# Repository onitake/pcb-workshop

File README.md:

PCB layouting workshop
======================

These are the example files and a short presentation for an
introduction to printed circuit board layouting with KiCad.

The design is loosely based on [Larry Ogrodnek's nametag](http://analogmachines.com/p/nametag/build/),
with some modifications and enhancements.
There's both through-hole and SMD versions.
The THT version is designed for 5mm LEDs, thus making it very
large. A new 3mm version is being worked on.

The software for the microcontroller is in [a separate project](https://github.com/nuess0r/am-nametag).

You can also find an example for a LED dot matrix display tag.
(currently broken, the pinout is wrong)

Description
-----------

The circuit is grouped in 4 parts:
- 5 LED blocks
- Transistor drivers for each block (based on 2N7002 N-FETs)
- ATtiny13 microcontoller
- CR2032 battery

Each block consists of a total of 20 LEDs in parallel, which can be
soldered on as desired.

It should be noted that the CR2032 has a high internal resistance
and can only deliver small currents, up to about 40mA.

The current-limiting resistors for each block should thus be
adjusted accordingly, to prevent brown-out of the MCU.
Note that the transistors also have a relatively high
on resistance.

If a Li-Ion or LiPo battery is used instead of the button
cell, much higher currents are possible.

The parts are fairly standard and can be ordered from any
supplier, such as Farnell, DigiKey, Reichelt, ...

License
-------

This documentation is copyright © 2016 by Chaostreff Basel and
describes Open Hardware and is licensed under the CERN OHL v. 1.2.
Please see the the [LICENSE](LICENSE) file for applicable conditions.

The author's contact information can be found in [AUTHORS](AUTHORS).

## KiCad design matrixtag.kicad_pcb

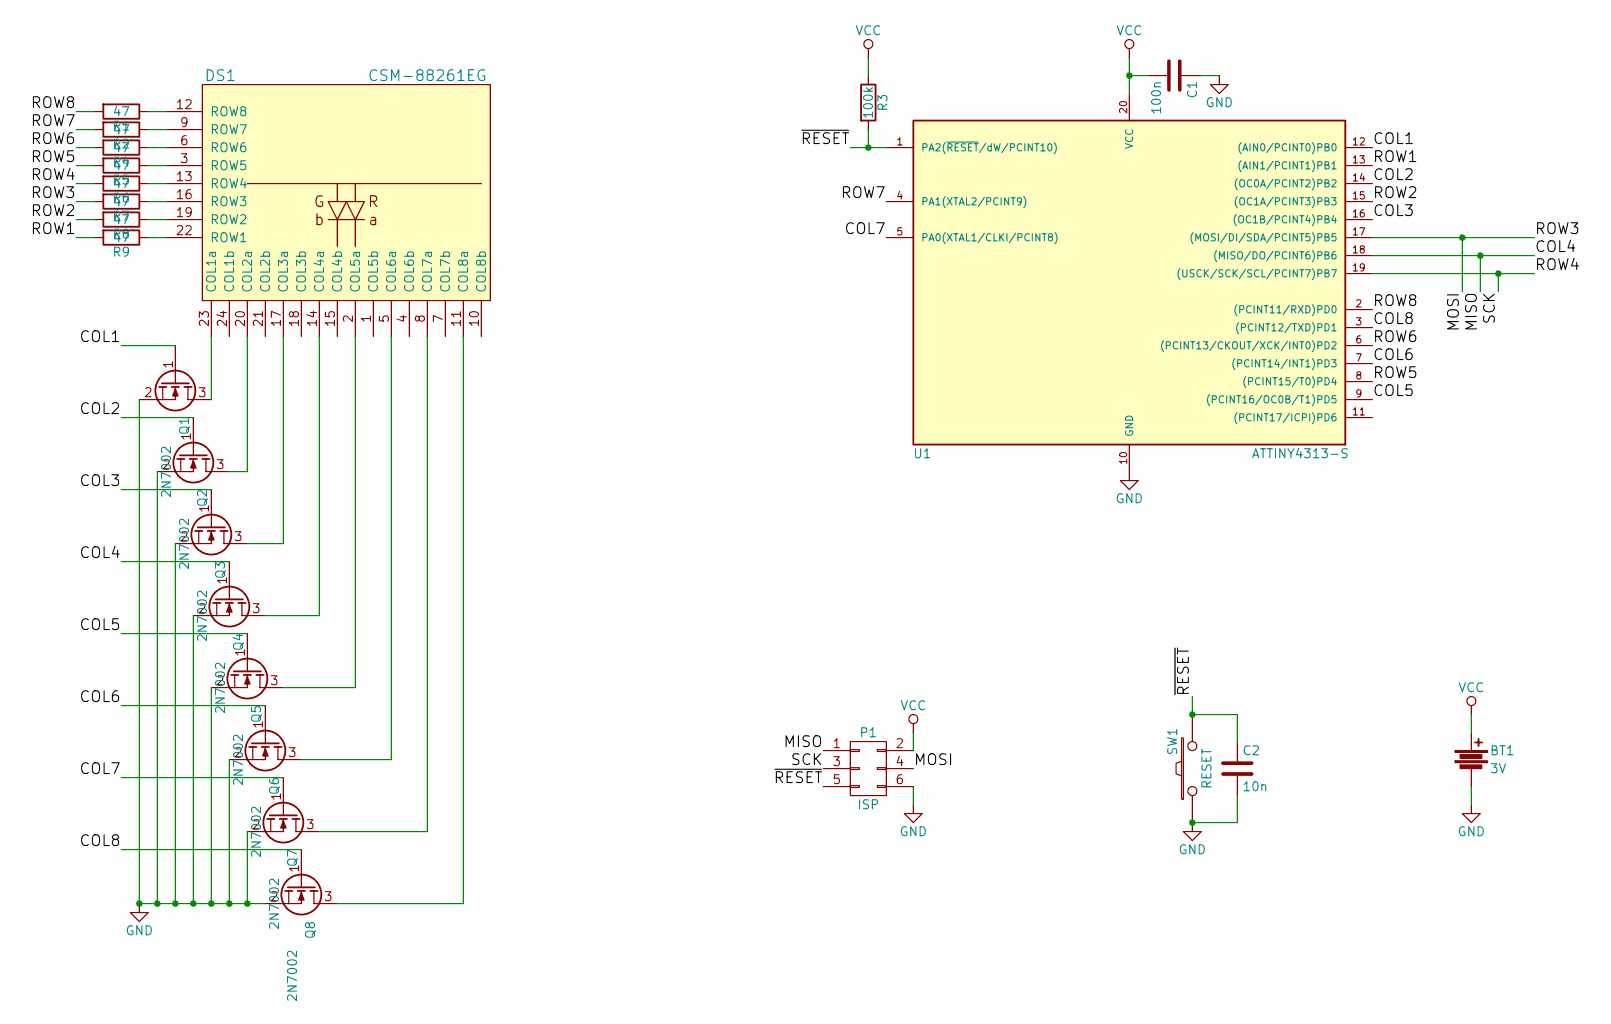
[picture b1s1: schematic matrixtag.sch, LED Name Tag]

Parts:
BT1: 3V; CR2032
C1: 100n; C_0805_HandSoldering
C2: 10n; C_0805_HandSoldering
DS1: CSM-88261EG; CSM-88261
P1: ISP; Pin_Header_Straight_2x03
Q1, Q2, Q3, Q4, Q5, Q6, Q7, Q8: 2N7002; SOT-23_Handsoldering
R1, R2, R4, R5, R6, R7, R8, R9: 47; R_0805_HandSoldering
R3: 100k; R_0805_HandSoldering
SW1: RESET; SW_PUSH_SMALL
U1: ATTINY4313-S; SOIC-20_7.5x12.8mm_Pitch1.27mm

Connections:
/COL1: Q1.1 (G), U1.12 ((AIN0/PCINT0)PB0)
/COL2: Q2.1 (G), U1.14 ((OC0A/PCINT2)PB2)
/COL3: Q3.1 (G), U1.16 ((OC1B/PCINT4)PB4)
/COL4: P1.1, Q4.1 (G), U1.18 ((MISO/DO/PCINT6)PB6)
/COL5: Q5.1 (G), U1.9 ((PCINT16/OC0B/T1)PD5)
/COL6: Q6.1 (G), U1.7 ((PCINT14/INT1)PD3)
/COL7: Q7.1 (G), U1.5 (PA0(XTAL1/CLKI/PCINT8))
/COL8: Q8.1 (G), U1.3 ((PCINT12/TXD)PD1)
/MOSI: P1.4, R7.2, U1.17 ((MOSI/DI/SDA/PCINT5)PB5)
/ROW1: R9.2, U1.13 ((AIN1/PCINT1)PB1)
/ROW2: R8.2, U1.15 ((OC1A/PCINT3)PB3)
/ROW4: P1.3, R6.2, U1.19 ((USCK/SCK/SCL/PCINT7)PB7)
/ROW5: R5.2, U1.8 ((PCINT15/T0)PD4)
/ROW6: R4.2, U1.6 ((PCINT13/CKOUT/XCK/INT0)PD2)
/ROW7: R2.2, U1.4 (PA1(XTAL2/PCINT9))
/ROW8: R1.2, U1.2 ((PCINT11/RXD)PD0)
/~RESET: C2.1, P1.5, R3.2, SW1.2, U1.1 (PA2(~RESET~/dW/PCINT10))
GND: BT1.2, C1.1, C2.2, P1.6, Q1.2 (S), Q2.2 (S), Q3.2 (S), Q4.2 (S), Q5.2 (S), Q6.2 (S), Q7.2 (S), Q8.2 (S), SW1.1, U1.10 (GND)
unnamed: DS1.2 (COL5a), Q5.3 (D)
unnamed: DS1.3 (ROW5), R5.1
unnamed: DS1.5 (COL6a), Q6.3 (D)
unnamed: DS1.6 (ROW6), R4.1
unnamed: DS1.8 (COL7a), Q7.3 (D)
unnamed: DS1.9 (ROW7), R2.1
unnamed: DS1.11 (COL8a), Q8.3 (D)
unnamed: DS1.12 (ROW8), R1.1
unnamed: DS1.13 (ROW4), R6.1
unnamed: DS1.14 (COL4a), Q4.3 (D)
unnamed: DS1.16 (ROW3), R7.1
unnamed: DS1.17 (COL3a), Q3.3 (D)
unnamed: DS1.19 (ROW2), R8.1
unnamed: DS1.20 (COL2a), Q2.3 (D)
unnamed: DS1.22 (ROW1), R9.1
unnamed: DS1.23 (COL1a), Q1.3 (D)
VCC: BT1.1, C1.2, P1.2, R3.1, U1.20 (VCC)

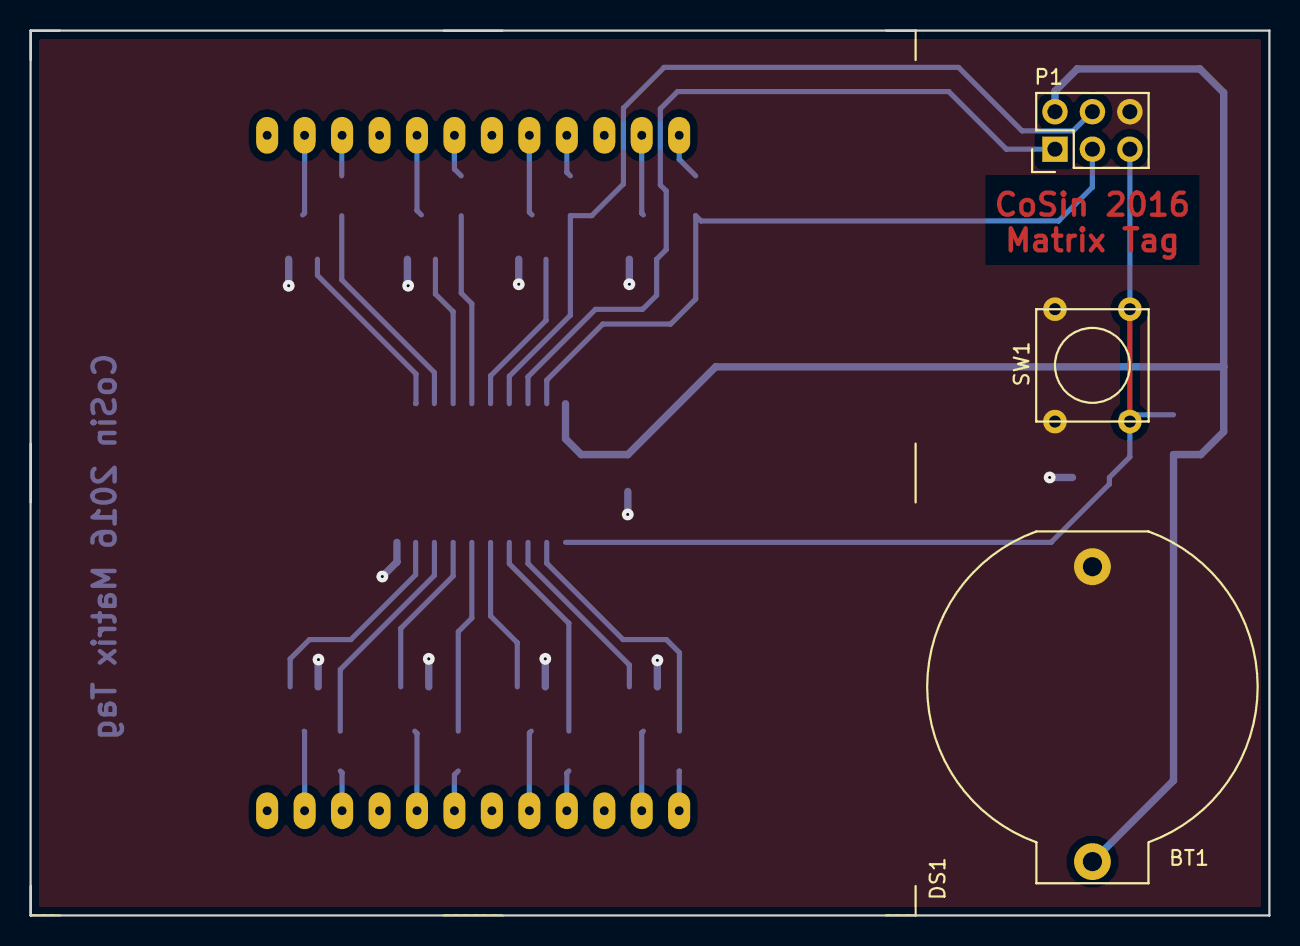
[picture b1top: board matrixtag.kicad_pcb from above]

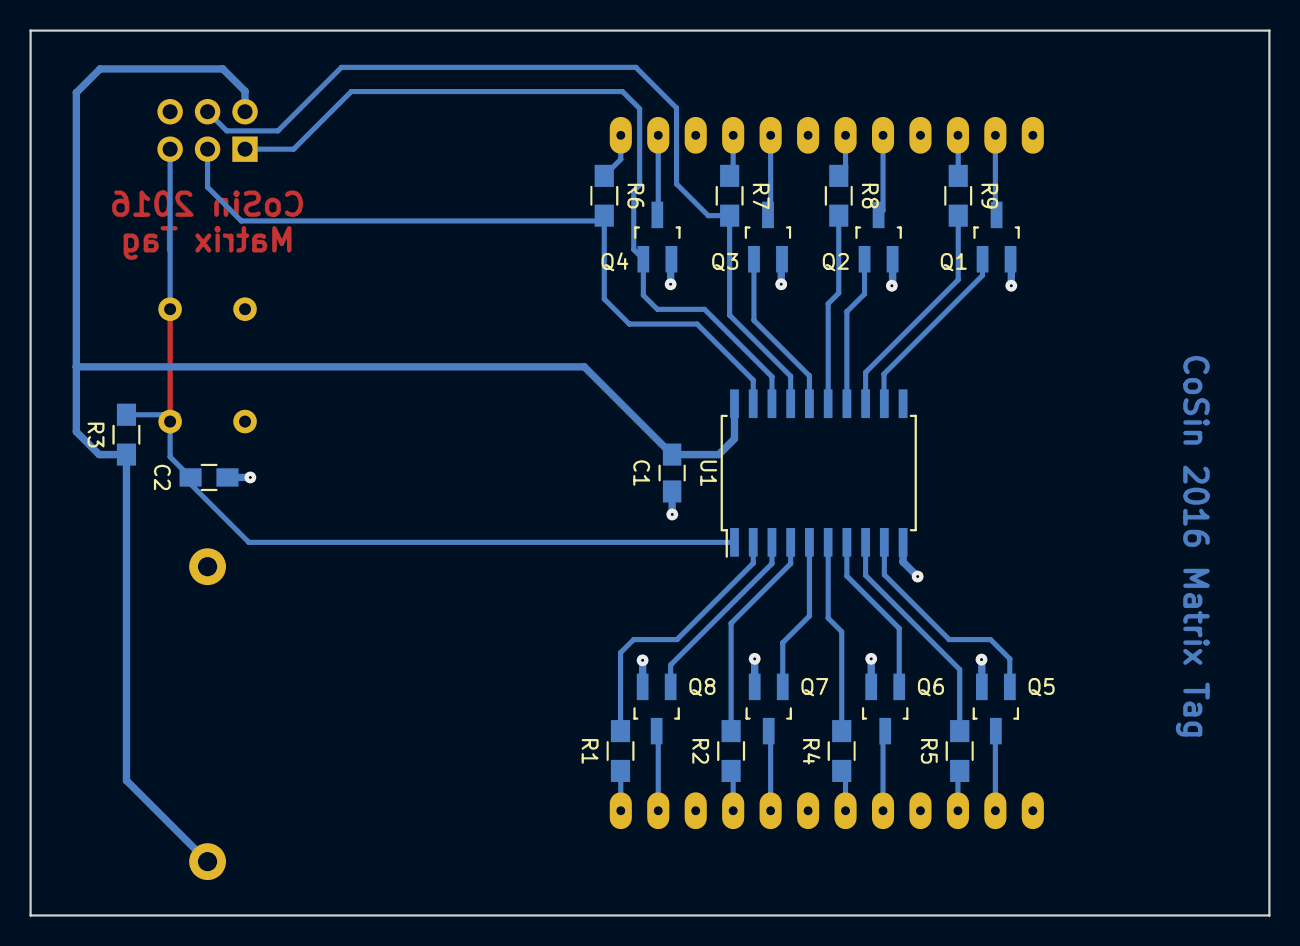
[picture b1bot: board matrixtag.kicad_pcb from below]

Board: 2 copper layers, 84.0 x 60.0 mm, 24 parts (20 on the bottom side), 35 nets.

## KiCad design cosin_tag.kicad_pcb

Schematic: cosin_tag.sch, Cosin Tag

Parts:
BT1: 3V; CR2032
C2: 100n; R_1206_HandSoldering
D1, D2, D3, D4, D5, D6, D7, D8, D9, D10, D21, D22, D23, D24, D25, D26, D27, D28, D29, D30, D31, D32, D41, D42, D43, D44, D45, D46, D47, D48, D49, D50, D51, D61, D62, D63, D64, D65, D81, D82, D83, D84, D85, D86, D87, D88, D89, D90, D91: LED; LED_0805
IC1: ATTINY13-SS; SOIC-8-N
JP1: RESET; SW_SPST_EVQP0
P1: ISP; Pin_Header_Straight_2x03
Q1, Q2, Q3, Q4, Q5: 2N7002; SOT-23_Handsoldering
R1, R2, R3, R4, R5: 0; R_0603_HandSoldering
R6: 100k; R_0603_HandSoldering

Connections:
/DIGIT0: IC1.2, Q1.1 (G)
/DIGIT1: IC1.3, Q2.1 (G)
/DIGIT2: IC1.7, P1.3, Q3.1 (G)
/DIGIT3: IC1.5, P1.4, Q4.1 (G)
/DIGIT4: IC1.6, P1.1, Q5.1 (G)
/~RESET: IC1.1, JP1.2, P1.5, R6.2
GND: BT1.2, C2.2, IC1.4, JP1.1, P1.6, Q1.2 (S), Q2.2 (S), Q3.2 (S), Q4.2 (S), Q5.2 (S)
unnamed: D1.1 (K), D2.1 (K), D3.1 (K), D4.1 (K), D5.1 (K), D6.1 (K), D7.1 (K), D8.1 (K), D9.1 (K), D10.1 (K), Q1.3 (D)
unnamed: D1.2 (A), D2.2 (A), D3.2 (A), D4.2 (A), D5.2 (A), D6.2 (A), D7.2 (A), D8.2 (A), D9.2 (A), D10.2 (A), R1.2
unnamed: D21.1 (K), D22.1 (K), D23.1 (K), D24.1 (K), D25.1 (K), D26.1 (K), D27.1 (K), D28.1 (K), D29.1 (K), D30.1 (K), D31.1 (K), D32.1 (K), Q2.3 (D)
unnamed: D21.2 (A), D22.2 (A), D23.2 (A), D24.2 (A), D25.2 (A), D26.2 (A), D27.2 (A), D28.2 (A), D29.2 (A), D30.2 (A), D31.2 (A), D32.2 (A), R2.2
unnamed: D41.1 (K), D42.1 (K), D43.1 (K), D44.1 (K), D45.1 (K), D46.1 (K), D47.1 (K), D48.1 (K), D49.1 (K), D50.1 (K), D51.1 (K), Q3.3 (D)
unnamed: D41.2 (A), D42.2 (A), D43.2 (A), D44.2 (A), D45.2 (A), D46.2 (A), D47.2 (A), D48.2 (A), D49.2 (A), D50.2 (A), D51.2 (A), R3.2
unnamed: D61.1 (K), D62.1 (K), D63.1 (K), D64.1 (K), D65.1 (K), Q4.3 (D)
unnamed: D61.2 (A), D62.2 (A), D63.2 (A), D64.2 (A), D65.2 (A), R4.2
unnamed: D81.1 (K), D82.1 (K), D83.1 (K), D84.1 (K), D85.1 (K), D86.1 (K), D87.1 (K), D88.1 (K), D89.1 (K), D90.1 (K), D91.1 (K), Q5.3 (D)
unnamed: D81.2 (A), D82.2 (A), D83.2 (A), D84.2 (A), D85.2 (A), D86.2 (A), D87.2 (A), D88.2 (A), D89.2 (A), D90.2 (A), D91.2 (A), R5.2
VCC: BT1.1, C2.1, IC1.8, P1.2, R1.1, R2.1, R3.1, R4.1, R5.1, R6.1

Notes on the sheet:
Coincell battery holder CR2032

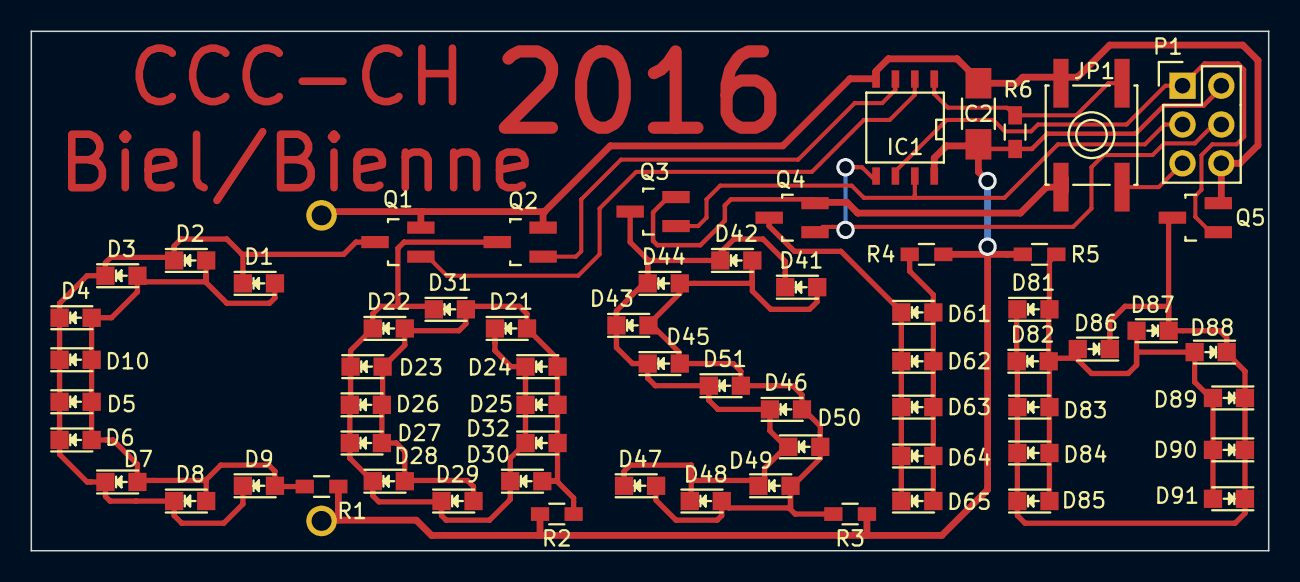
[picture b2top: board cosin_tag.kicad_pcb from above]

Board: 2 copper layers, 81.0 x 34.0 mm, 65 parts (1 on the bottom side), 18 nets.

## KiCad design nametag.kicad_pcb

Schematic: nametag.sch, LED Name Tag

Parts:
BT1: 3V; CR2032
C2: 100n; C_Disc_D3_P2.5
D1, D2, D3, D4, D5, D6, D7, D8, D9, D10, D11, D12, D13, D14, D15, D16, D17, D18, D19, D20, D21, D22, D23, D24, D25, D26, D27, D28, D29, D30, D31, D32, D33, D34, D35, D36, D37, D38, D39, D40, D41, D42, D43, D44, D45, D46, D47, D48, D49, D50, D51, D52, D53, D54, D55, D56, D57, D58, D59, D60, D61, D62, D63, D64, D65, D66, D67, D68, D69, D70, D71, D72, D73, D74, D75, D76, D77, D78, D79, D80, D81, D82, D83, D84, D85, D86, D87, D88, D89, D90, D91, D92, D93, D94, D95, D96, D97, D98, D99, D100: LED; LED-5MM
JP1: RESET; SW_PUSH_SMALL
P1: ISP; Pin_Header_Straight_2x03
Q1, Q2, Q3, Q4, Q5: 2N7002; SOT-23_Handsoldering
R1, R2, R3, R4, R5: 0; Resistor_Horizontal_RM10mm
R6: 100k; Resistor_Horizontal_RM10mm
U1: ATTINY13-SS; DIP-8_W7.62mm

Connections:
/DIGIT0: Q1.1 (G), U1.2
/DIGIT1: Q2.1 (G), U1.3
/DIGIT2: P1.3, Q3.1 (G), U1.7
/DIGIT3: P1.4, Q4.1 (G), U1.5
/DIGIT4: P1.1, Q5.1 (G), U1.6
/~RESET: JP1.1, P1.5, R6.2, U1.1
GND: BT1.2, C2.2, JP1.2, P1.6, Q1.2 (S), Q2.2 (S), Q3.2 (S), Q4.2 (S), Q5.2 (S), U1.4
unnamed: D1.1 (K), D2.1 (K), D3.1 (K), D4.1 (K), D5.1 (K), D6.1 (K), D7.1 (K), D8.1 (K), D9.1 (K), D10.1 (K), D11.1 (K), D12.1 (K), D13.1 (K), D14.1 (K), D15.1 (K), D16.1 (K), D17.1 (K), D18.1 (K), D19.1 (K), D20.1 (K), Q1.3 (D)
unnamed: D1.2 (A), D2.2 (A), D3.2 (A), D4.2 (A), D5.2 (A), D6.2 (A), D7.2 (A), D8.2 (A), D9.2 (A), D10.2 (A), D11.2 (A), D12.2 (A), D13.2 (A), D14.2 (A), D15.2 (A), D16.2 (A), D17.2 (A), D18.2 (A), D19.2 (A), D20.2 (A), R1.2
unnamed: D21.1 (K), D22.1 (K), D23.1 (K), D24.1 (K), D25.1 (K), D26.1 (K), D27.1 (K), D28.1 (K), D29.1 (K), D30.1 (K), D31.1 (K), D32.1 (K), D33.1 (K), D34.1 (K), D35.1 (K), D36.1 (K), D37.1 (K), D38.1 (K), D39.1 (K), D40.1 (K), Q2.3 (D)
unnamed: D21.2 (A), D22.2 (A), D23.2 (A), D24.2 (A), D25.2 (A), D26.2 (A), D27.2 (A), D28.2 (A), D29.2 (A), D30.2 (A), D31.2 (A), D32.2 (A), D33.2 (A), D34.2 (A), D35.2 (A), D36.2 (A), D37.2 (A), D38.2 (A), D39.2 (A), D40.2 (A), R2.2
unnamed: D41.1 (K), D42.1 (K), D43.1 (K), D44.1 (K), D45.1 (K), D46.1 (K), D47.1 (K), D48.1 (K), D49.1 (K), D50.1 (K), D51.1 (K), D52.1 (K), D53.1 (K), D54.1 (K), D55.1 (K), D56.1 (K), D57.1 (K), D58.1 (K), D59.1 (K), D60.1 (K), Q3.3 (D)
unnamed: D41.2 (A), D42.2 (A), D43.2 (A), D44.2 (A), D45.2 (A), D46.2 (A), D47.2 (A), D48.2 (A), D49.2 (A), D50.2 (A), D51.2 (A), D52.2 (A), D53.2 (A), D54.2 (A), D55.2 (A), D56.2 (A), D57.2 (A), D58.2 (A), D59.2 (A), D60.2 (A), R3.2
unnamed: D61.1 (K), D62.1 (K), D63.1 (K), D64.1 (K), D65.1 (K), D66.1 (K), D67.1 (K), D68.1 (K), D69.1 (K), D70.1 (K), D71.1 (K), D72.1 (K), D73.1 (K), D74.1 (K), D75.1 (K), D76.1 (K), D77.1 (K), D78.1 (K), D79.1 (K), D80.1 (K), Q4.3 (D)
unnamed: D61.2 (A), D62.2 (A), D63.2 (A), D64.2 (A), D65.2 (A), D66.2 (A), D67.2 (A), D68.2 (A), D69.2 (A), D70.2 (A), D71.2 (A), D72.2 (A), D73.2 (A), D74.2 (A), D75.2 (A), D76.2 (A), D77.2 (A), D78.2 (A), D79.2 (A), D80.2 (A), R4.2
unnamed: D81.1 (K), D82.1 (K), D83.1 (K), D84.1 (K), D85.1 (K), D86.1 (K), D87.1 (K), D88.1 (K), D89.1 (K), D90.1 (K), D91.1 (K), D92.1 (K), D93.1 (K), D94.1 (K), D95.1 (K), D96.1 (K), D97.1 (K), D98.1 (K), D99.1 (K), D100.1 (K), Q5.3 (D)
unnamed: D81.2 (A), D82.2 (A), D83.2 (A), D84.2 (A), D85.2 (A), D86.2 (A), D87.2 (A), D88.2 (A), D89.2 (A), D90.2 (A), D91.2 (A), D92.2 (A), D93.2 (A), D94.2 (A), D95.2 (A), D96.2 (A), D97.2 (A), D98.2 (A), D99.2 (A), D100.2 (A), R5.2
VCC: BT1.1, C2.1, P1.2, R1.1, R2.1, R3.1, R4.1, R5.1, R6.1, U1.8

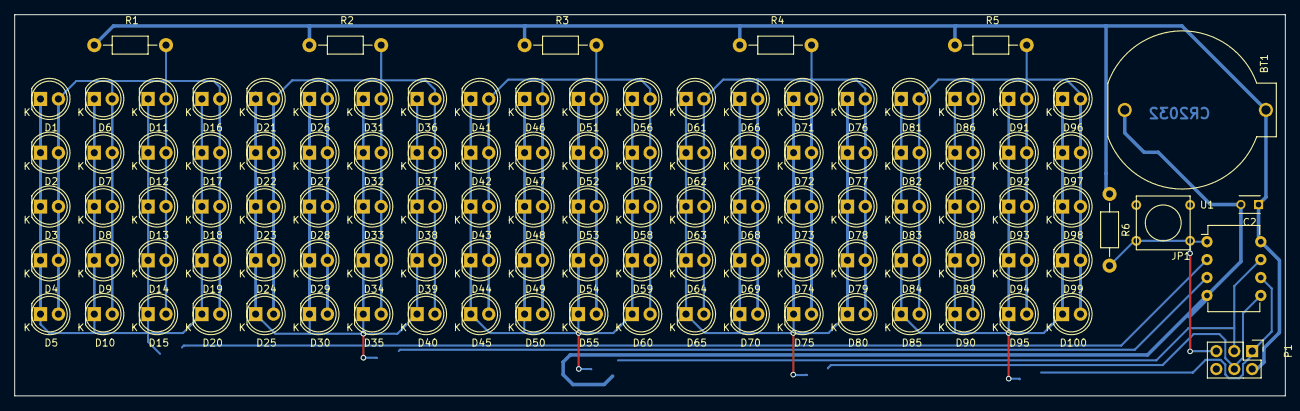
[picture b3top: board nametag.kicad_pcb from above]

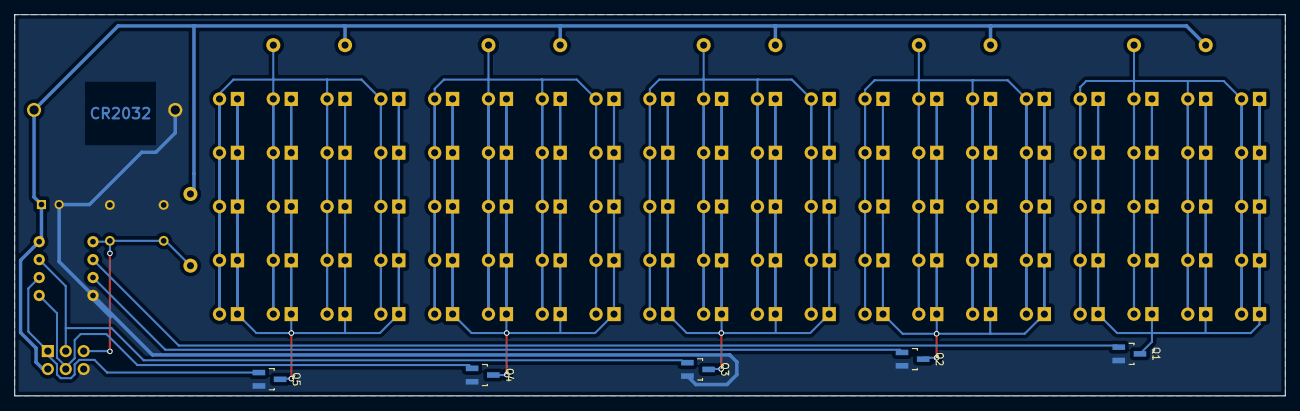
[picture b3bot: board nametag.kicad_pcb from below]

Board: 2 copper layers, 180.0 x 54.0 mm, 116 parts (5 on the bottom side), 18 nets.

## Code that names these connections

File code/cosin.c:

/* 
 * cosin.c
 * 
 * CoSin 2016 LED Matrix Tag
 * Controller firmware
 * 
 * Copyright (c) 2016 Gregor Riepl <onitake@gmail.com>
 * 
 * This documentation describes Open Hardware and is licensed under the
 * CERN OHL v. 1.1.
 * You may redistribute and modify this documentation under the terms of the
 * CERN OHL v.1.1. (http://ohwr.org/cernohl). This documentation is distributed
 * WITHOUT ANY EXPRESS OR IMPLIED WARRANTY, INCLUDING OF
 * MERCHANTABILITY, SATISFACTORY QUALITY AND FITNESS FOR A
 * PARTICULAR PURPOSE. Please see the CERN OHL v.1.1 for applicable
 * conditions
*/

#include <avr/io.h>
#include <avr/interrupt.h>
#include <avr/pgmspace.h>
#include <util/delay.h>
#include <stdint.h>
#include <stdbool.h>
#include <string.h>
#include "map.h"

// Global state
struct {
	// The framebuffer
	// in column-major order
	uint8_t fb[8];
	// Current column
	uint8_t col;
	// Letter index
	uint8_t scene;
	// Horizontal offset
	uint8_t offset;
} global __attribute__((section(".noinit")));

const char MESSAGE[] PROGMEM = "COSIN 2016 ";
extern const unsigned char FONT_SANS8X8[][8] PROGMEM;
extern const unsigned char FONTMAP_SANS8X8[] PROGMEM;

// Initalize ports and timers
void init() {
	global.col = 0;
	memset(global.fb, 0, 8*8);
	global.scene = 0;
	global.offset = 0;

	PORTB &= ~0xff;
	DDRB |= 0xff;
	PORTD &= ~0x3f;
	DDRD |= 0x3f;
	PORTA &= ~0x03;
	DDRA |= 0x03;
	
	OCR1A = F_CPU / 1024 / 8;
	TIMSK |= _BV(TOIE1);
	// Fast PWM, TOP in OCR1A
	TCCR1A = _BV(WGM11) | _BV(WGM10);
	// CLKio / 1024
	TCCR1B = _BV(WGM13) | _BV(WGM12) | _BV(CS12) | _BV(CS10);
}

// Write a letter to the framebuffer
void wrletter(char letter, int8_t xoffset) {
	uint8_t xstart, xlen;
	if (xoffset < 0) {
		if (xoffset >= -8) {
			xstart = -xoffset;
			xlen = 8 + xoffset;
		} else {
			xstart = 0;
			xlen = 0;
		}
		xoffset = 0;
	} else if (xoffset >= 0) {
		if (xoffset < 8) {
			xlen = 8 - xoffset;
		} else {
			xlen = 0;
		}
		xstart = 0;
	}
	if (xlen > 0) {
		uint8_t index = pgm_read_byte(&FONTMAP_SANS8X8[(uint8_t) letter]);
		memcpy_P(global.fb + xoffset, FONT_SANS8X8[index] + xstart, xlen);
	}
}

// Refresh the display (one column at a time)
void refresh() {
	// Port map
	// COL1: PB1
	// COL2: PB3
	// COL3: PB5
	// COL4: PB7
	// COL5: PD5
	// COL6: PD3
	// COL7: PA0
	// COL8: PD1
	// ROW1: PB0
	// ROW2: PB2
	// ROW3: PB4
	// ROW4: PB6
	// ROW5: PD4
	// ROW6: PD2
	// ROW7: PA1
	// ROW8: PD0
	
	// Wiring
	// COL is driven by MOSFETs, while ROW is driven directly by MCU
	// Switch COL first, then present ROW bit pattern
	
	uint8_t bitmap = global.fb[global.col];
	uint8_t pa = 0, pb = 0, pd = 0;

	// switch is no good here - it will make avr-gcc allocate and
	// initialize 18 bytes of .data space for the lookup table - WTF!
	uint8_t col = global.col;
	if (col == 0) {
		pb |= _BV(1);
	} else if (col == 1) {
		pb |= _BV(3);
	} else if (col == 2) {
		pb |= _BV(5);
	} else if (col == 3) {
		pb |= _BV(7);
	} else if (col == 4) {
		pd |= _BV(5);
	} else if (col == 5) {
		pd |= _BV(3);
	} else if (col == 6) {
		pa |= _BV(0);
	} else if (col == 7) {
		pd |= _BV(1);
	}
	
	if (bitmap & _BV(0)) {
		pb |= _BV(0);
	}
	if (bitmap & _BV(1)) {
		pb |= _BV(2);
	}
	if (bitmap & _BV(2)) {
		pb |= _BV(4);
	}
	if (bitmap & _BV(3)) {
		pb |= _BV(6);
	}
	if (bitmap & _BV(4)) {
		pd |= _BV(4);
	}
	if (bitmap & _BV(5)) {
		pd |= _BV(2);
	}
	if (bitmap & _BV(6)) {
		pa |= _BV(1);
	}
	if (bitmap & _BV(7)) {
		pd |= _BV(0);
	}

	PORTA = pa;
	PORTB = pb;
	PORTD = pd;
	
	global.col = (global.col + 1) & 0x7;
}

// Update the display
ISR(TIMER1_OVF_vect) {
#if 0
	uint8_t col = global.scene >> 3;
	uint8_t row = global.scene & 0x07;
	uint8_t i;
	for (i = 0; i < 8; i++) {
		if (row == i) {
			global.fb[i] = 1 << col;
		} else {
			global.fb[i] = 0x00;
		}
	}
	global.scene = (global.scene + 1) & 0x3f;
#else
	wrletter(pgm_read_byte(&MESSAGE[global.scene]), -global.offset);
	uint8_t next;
	if (global.scene < sizeof(MESSAGE) - 2) {
		next = global.scene + 1;
	} else {
		next = 0;
	}
	wrletter(pgm_read_byte(&MESSAGE[next]), 8 - global.offset);
	if (global.offset >= 7) {
		global.scene = next;
		global.offset = 0;
	} else {
		global.offset++;
	}
#endif
}

int main() {
	init();
	
#if 1
	wrletter(pgm_read_byte(&MESSAGE[0]), 0);
	
	sei();
	
	while (true) {
		refresh();
	}
#else

	// COL1: PB7
	// COL2: PB5
	// COL3: PB3
	// COL4: PB1
	// COL5: PD5
	// COL6: PD3
	// COL7: PA0
	// COL8: PD1
	// ROW1: PB6
	// ROW2: PB4
	// ROW3: PB2
	// ROW4: PB0
	// ROW5: PD4
	// ROW6: PD2
	// ROW7: PA1
	// ROW8: PD0
	
	PORTB |= 0xff;
	PORTD |= 0x3f;
	PORTA |= 0x03;
	while (1);

	uint8_t pb = 0;
	uint8_t pd = 0;
	uint8_t pa = 0;
	
	while (1) {
		PORTB = pb;
		PORTD = pd;
		PORTA = pa;
		
		if (pb == 0xff) {
			if (pd == 0x3f) {
				if (pa == 0x3) {
					pa = 0;
				} else {
					pa++;
				}
			}
			pd++;
		}
		pb++;

		_delay_ms(10);
	}
	
#endif

	return 0;
}

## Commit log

2016-04-11 First version of example name tag board
2016-04-11 Added LED matrix example schema
2016-04-11 Added readme and license
2016-04-12 Added schematics and unrouted PCB of matrix display nametag
2016-04-23 Improved ground plane area
2016-04-23 Moved parts to front layer
2016-06-04 Fixed reset button rail mismatch Added missing traces (GND) Replaced reset button by 4-pin standard part
2016-06-04 Added SMD version of the nametag project using 0805 SMD LEDs.
2016-06-04 Added missing library components.
    Cleaned up a bit the area under the switch to make PCB production easier.
2016-06-08 Changed the package variant of the ATTINY13 to SO-8 narrow (ATTINY13-SS) because it is cheaper.
    Fixed wrong ISP pinning.
    Cleaned up the older thiner pcb tracks.
2016-06-10 Connected Vcc to ISP header Better GND routing in layout
2016-06-10 Added presentation slides
2016-06-10 Added production outputs (needs update)
2016-06-11 Created a tag version for the CoSin conference 2016 in Biel/Bienne.
2016-06-11 Added schematic and pcb outputs as PDF for the nametag SMD and the cosin version.
2016-06-13 THT nametag: Removed Vcc jumper wire
2016-06-13 Updated DIY fabriction outputs
2016-06-13 Added SMD battery holder footprint
2016-06-13 Moved SMD battery holder footprint to main library
2016-06-13 Finished matrix tag schematic and layout
2016-06-13 Added "wear safety goggles" warning sign
2016-06-13 Project date bump
2016-06-13 Added datasheet URLs
2016-06-13 Added datasheet PDFs to ignore list
2016-06-13 Added symbol and footprint for 2-color 8x8 matrix display
2016-06-13 Added author list
2016-06-15 Minimized the areas in the layout where the tracks are close together. Made the tracks around the microcontroller smaller to improve yield when etching the PCB at home. For this a new netclass was in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
    Added the resistor values to the schematic.
    Updated all output files.
2016-06-21 Some small matrix tag updates
2016-06-23 Fixed pinout of LED matrix footprint
2016-06-23 Fixed matrix tag layout with correct panel pinout
2016-06-23 Updated matrix tag schematic and PCB output
2016-06-23 Added Gerber files for matrix tag
2016-06-23 Added source code for matrix tag
2016-06-23 Updated gitignore
2016-06-30 Added new font generator
2016-06-30 Added basic bold 8x8 font (for CoSin2016 badge)
2016-06-30 Switched to new 8x8 font
2016-06-30 Removed old hand-coded font
2016-07-05 Fixed font generation make rule
2016-07-05 Implemented text scrolling effect
2016-07-06 Improved 2 glyph
2016-07-06 Fixed display of 0 terminator Increased banner speed
